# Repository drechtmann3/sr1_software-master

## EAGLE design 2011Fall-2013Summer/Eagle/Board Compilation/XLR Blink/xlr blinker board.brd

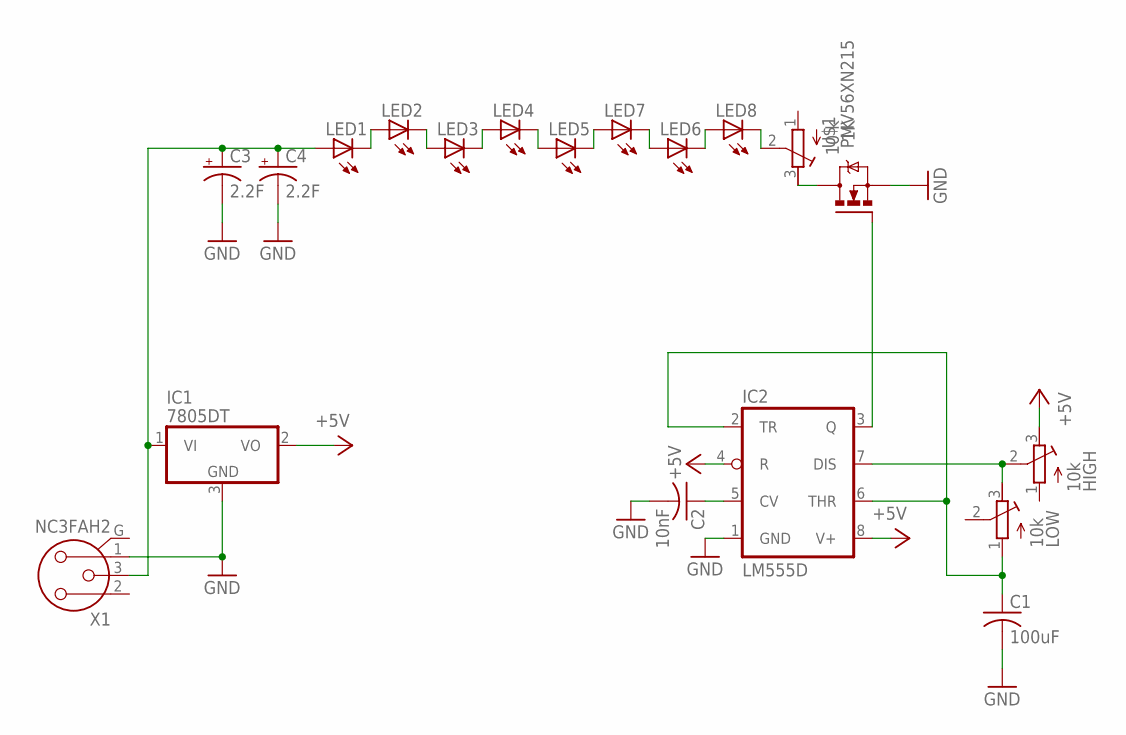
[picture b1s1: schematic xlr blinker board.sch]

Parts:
1K: 10 k; RTRIM3314J
C1: 100uF; C1206
C2: 10nF; C1206
C3, C4: 2.2F; E5-10,5
HIGH: 10k; RTRIM3314J
IC1: 7805DT; TO252
IC2: LM555D; SO08
LED1, LED2, LED3, LED4, LED5, LED6, LED7, LED8: LEDCHIPLED_1206; CHIPLED_1206
LOW: 10k; RTRIM3314J
U$1: PMV56XN215; SOT23; PART_NUM PMV56XN,215
X1: NC3FAH2

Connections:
24V: C3.+, C4.+, IC1.1 (VI), LED1.A, X1.3
+5V: HIGH.3 (A), IC1.2 (VO), IC2.4 (R), IC2.8 (V+)
GND: C1.2, C2.2, C3.-, C4.-, IC1.3 (GND), IC2.1 (GND), U$1.2 (S), X1.1 (2)
unnamed: HIGH.2 (S), IC2.7 (DIS), LOW.3 (A)
unnamed: C1.1, IC2.2 (TR), IC2.6 (THR), LOW.1 (E)
unnamed: C2.1, IC2.5 (CV)
unnamed: 1K.2 (S), LED8.C
unnamed: LED1.C, LED2.A
unnamed: 1K.3 (A), U$1.3 (D)
unnamed: IC2.3 (Q), U$1.1 (G)
unnamed: LED2.C, LED3.A
unnamed: LED3.C, LED4.A
unnamed: LED4.C, LED5.A
unnamed: LED5.C, LED7.A
unnamed: LED6.A, LED7.C
unnamed: LED6.C, LED8.A

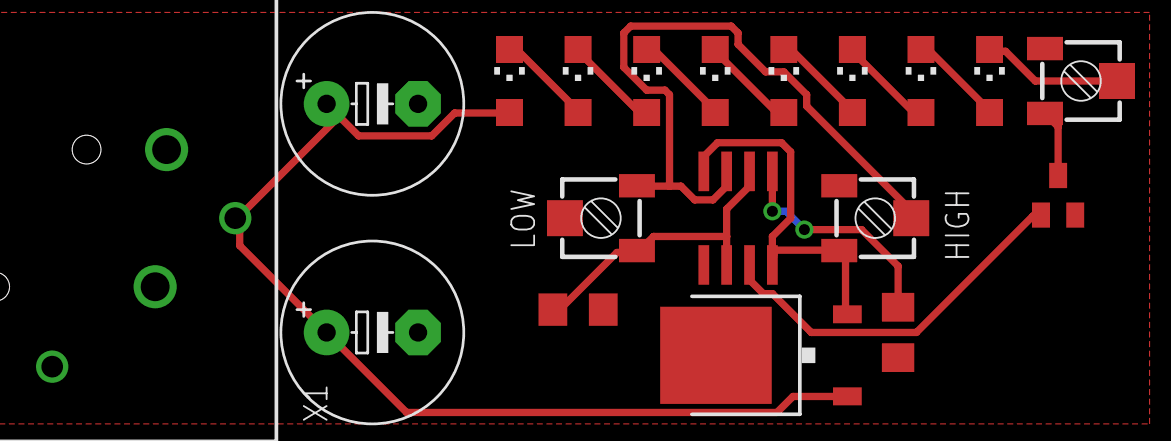
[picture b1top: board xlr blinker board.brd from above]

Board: 2 copper layers, 19 parts (0 on the bottom side), 16 nets.

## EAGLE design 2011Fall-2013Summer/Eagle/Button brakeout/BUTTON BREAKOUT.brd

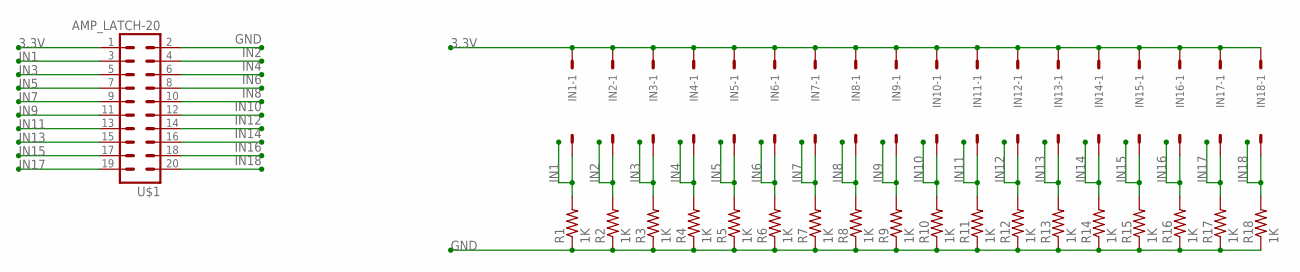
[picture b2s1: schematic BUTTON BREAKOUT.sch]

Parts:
IN1, IN2, IN3, IN4, IN5, IN6, IN7, IN8, IN9, IN10, IN11, IN12, IN13, IN14, IN15, IN16, IN17, IN18: C-GRID-02-70543; 70543-02
R1, R2, R3, R4, R5, R6, R7, R8, R9, R10, R11, R12, R13, R14, R15, R16, R17, R18: 1K; R1206
U$1: AMP_LATCH-20; MA10-2

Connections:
3.3V: IN1.1, IN2.1, IN3.1, IN4.1, IN5.1, IN6.1, IN7.1, IN8.1, IN9.1, IN10.1, IN11.1, IN12.1, IN13.1, IN14.1, IN15.1, IN16.1, IN17.1, IN18.1, U$1.1
GND: R1.1, R2.1, R3.1, R4.1, R5.1, R6.1, R7.1, R8.1, R9.1, R10.1, R11.1, R12.1, R13.1, R14.1, R15.1, R16.1, R17.1, R18.1, U$1.2
IN1: IN1.2, R1.2, U$1.3
IN2: IN2.2, R2.2, U$1.4
IN3: IN3.2, R3.2, U$1.5
IN4: IN4.2, R4.2, U$1.6
IN5: IN5.2, R5.2, U$1.7
IN6: IN6.2, R6.2, U$1.8
IN7: IN7.2, R7.2, U$1.9
IN8: IN8.2, R8.2, U$1.10
IN9: IN9.2, R9.2, U$1.11
IN10: IN10.2, R10.2, U$1.12
IN11: IN11.2, R11.2, U$1.13
IN12: IN12.2, R12.2, U$1.14
IN13: IN13.2, R13.2, U$1.15
IN14: IN14.2, R14.2, U$1.16
IN15: IN15.2, R15.2, U$1.17
IN16: IN16.2, R16.2, U$1.18
IN17: IN17.2, R17.2, U$1.19
IN18: IN18.2, R18.2, U$1.20

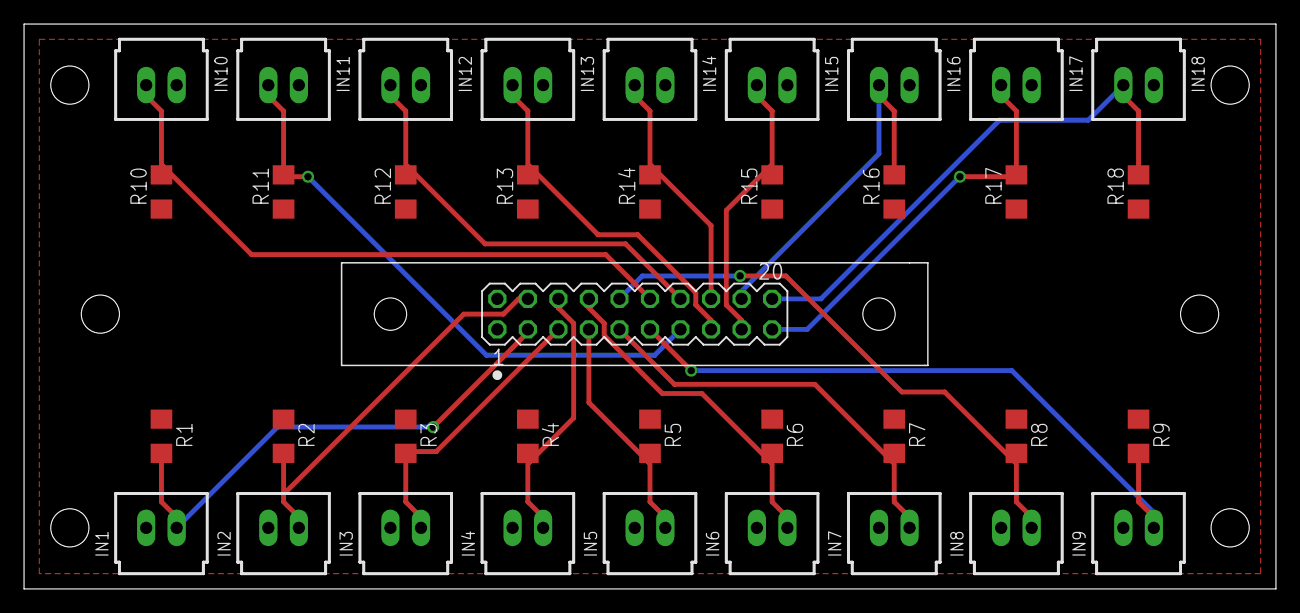
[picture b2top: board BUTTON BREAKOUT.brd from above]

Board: 2 copper layers, 104.1 x 47.0 mm, 37 parts (0 on the bottom side), 20 nets.

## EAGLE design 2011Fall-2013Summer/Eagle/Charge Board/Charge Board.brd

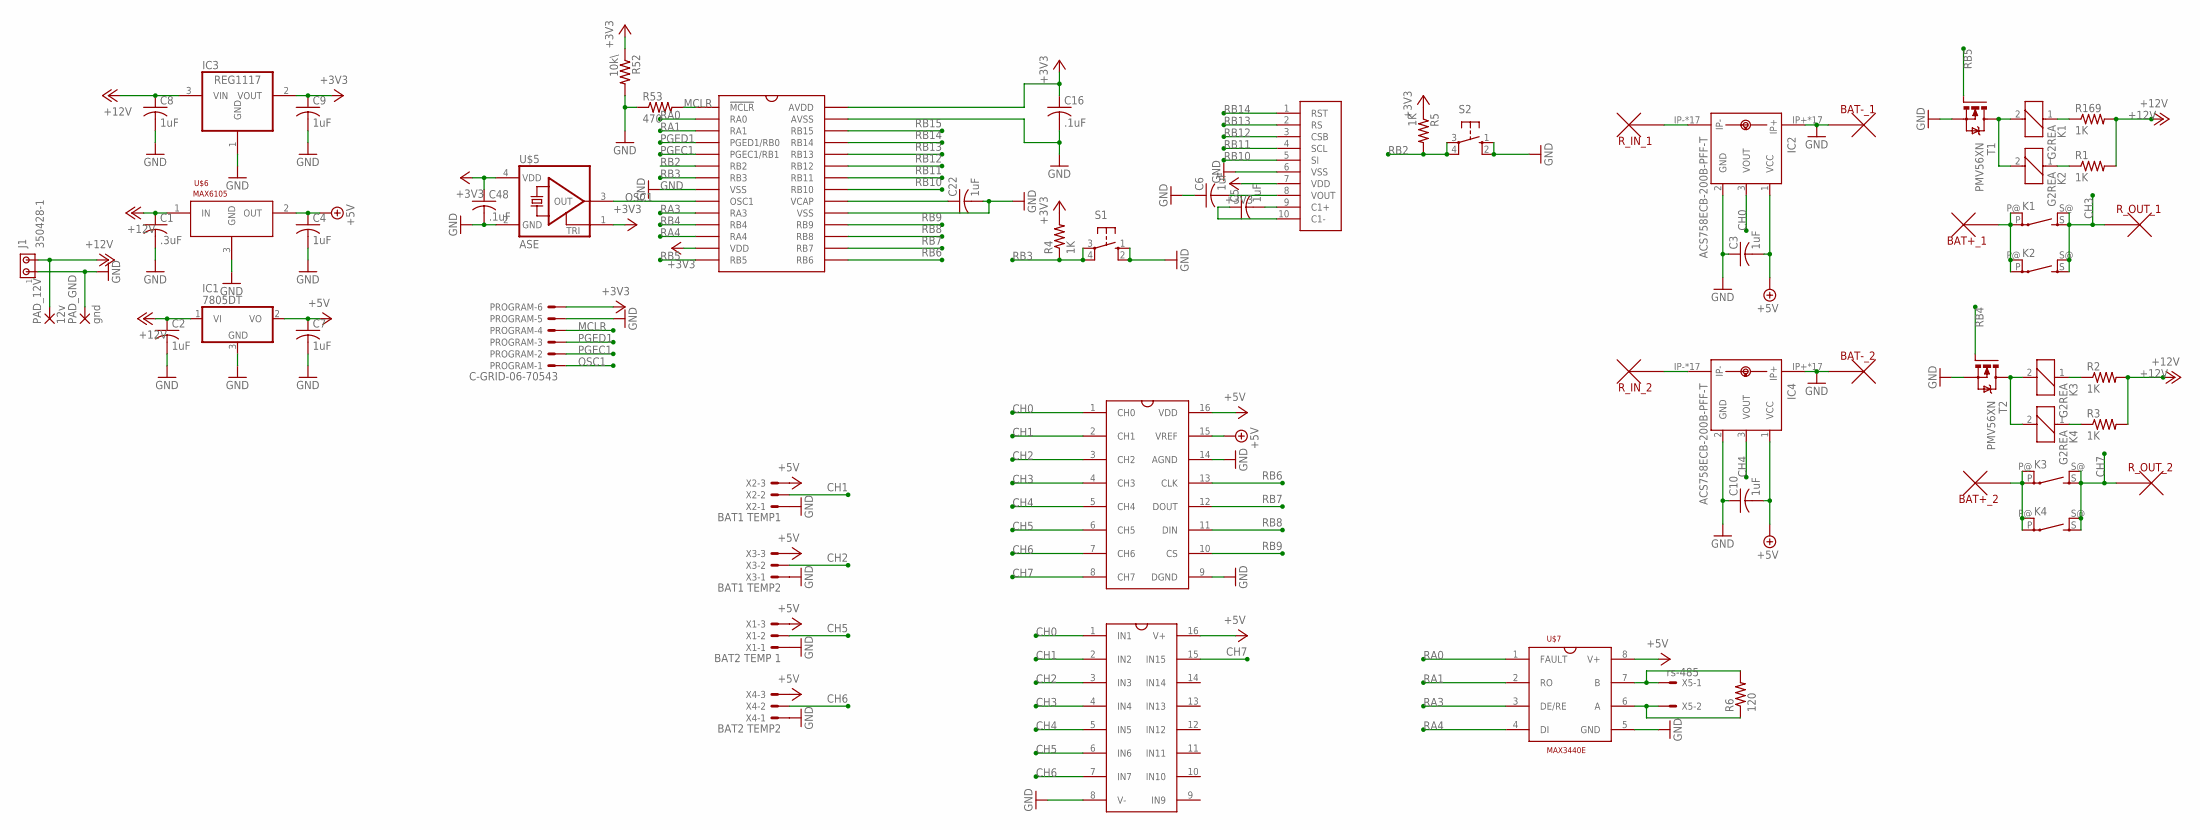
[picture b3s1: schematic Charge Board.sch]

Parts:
BAT+_1: BAT1 +; SOLDERPAD
BAT+_2: BAT2 +; SOLDERPAD
BAT-_1: BAT1 GND; SOLDERPAD
BAT-_2: BAT2 GND; SOLDERPAD
C1: .3uF; C1206
C2, C3, C4, C5, C6, C7, C8, C9, C10, C22: 1uF; C1206
C16, C48: .1uF; C1206
IC1: 7805DT; TO252
IC2, IC4: ACS758ECB-200B-PFF-T; CB-PFF
IC3: REG1117; SOT223
J1: 350428-1
K1, K2, K3, K4: G2REA
PAD_12V: 12v; 3,81/1,4
PAD_GND: gnd; 3,81/1,4
PROGRAM: C-GRID-06-70543; 70543-06
R1, R2, R3, R4, R5, R169: 1K; R1206
R6: 120; R1206
R52: 10k\; R1206
R53: 470; R1206
R_IN_1: R1 IN; SOLDERPAD
R_IN_2: R2 IN; SOLDERPAD
R_OUT_1: R1 OUT; SOLDERPAD
R_OUT_2: R2 OUT; SOLDERPAD
S1, S2: 10-XX; B3F-10XX
T1, T2: PMV56XN; SOT23
U$1: MCP-3008; SO16
U$2: LCD_SCREEN
U$3: SP720APP; SO16
U$4: PIC24HJ128GP-202; SO28W
U$5: ASE
U$6: MAX6105; SOT23
U$7: MAX3440E; SO-08
X1: BAT2 TEMP 1; 70543-03
X2: BAT1 TEMP1; 70543-03
X3: BAT1 TEMP2; 70543-03
X4: BAT2 TEMP2; 70543-03
X5: rs-485; 70543-02

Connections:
+3V3: C9.1, C16.1, C48.1, IC3.2 (VOUT), PROGRAM.6, R4.2, R5.1, R52.1, U$2.7 (VDD), U$4.13 (VDD), U$4.28 (AVDD), U$5.1 (TRI), U$5.4 (VDD)
+5V: C3.2, C4.1, C7.1, C10.2, IC1.2 (VO), IC2.1 (VCC), IC4.1 (VCC), U$1.15 (VREF), U$1.16 (VDD), U$3.16 (V+), U$6.2 (OUT), U$7.8 (V+), X1.3, X2.3, X3.3, X4.3
+12V: C1.1, C2.1, C8.1, IC1.1 (VI), IC3.3 (VIN), J1.2, PAD_12V.1, R1.2, R2.2, R3.2, R169.2, U$6.1 (IN)
CH0: IC2.3 (VOUT), U$1.1 (CH0), U$3.1 (IN1)
CH1: U$1.2 (CH1), U$3.2 (IN2), X2.2
CH2: U$1.3 (CH2), U$3.3 (IN3), X3.2
CH3: K1.S, K1.S@ (S), K2.S, K2.S@ (S), R_OUT_1.P$1, U$1.4 (CH3), U$3.4 (IN4)
CH4: IC4.3 (VOUT), U$1.5 (CH4), U$3.5 (IN5)
CH5: U$1.6 (CH5), U$3.6 (IN6), X1.2
CH6: U$1.7 (CH6), U$3.7 (IN7), X4.2
CH7: K3.S, K3.S@ (S), K4.S, K4.S@ (S), R_OUT_2.P$1, U$1.8 (CH7), U$3.15 (IN15)
GND: BAT-_1.P$1, BAT-_2.P$1, C1.2, C2.2, C3.1, C4.2, C6.1, C7.2, C8.2, C9.2, C10.1, C16.2, C22.2, C48.2, IC1.3 (GND), IC2.2 (GND), IC2.IP+, IC2.IP+@2 (IP+), IC2.IP+@3 (IP+), IC2.IP+@4 (IP+), IC2.IP+@5 (IP+), IC2.IP+@6 (IP+), IC2.IP+@7 (IP+), IC2.IP+@8 (IP+), IC2.IP+@9 (IP+), IC2.IP+@10 (IP+), IC2.IP+@11 (IP+), IC2.IP+@12 (IP+), IC2.IP+@13 (IP+), IC2.IP+@14 (IP+), IC2.IP+@15 (IP+), IC2.IP+@16 (IP+), IC2.IP+@17 (IP+), IC3.1 (GND), IC4.2 (GND), IC4.IP+, IC4.IP+@2 (IP+), IC4.IP+@3 (IP+), IC4.IP+@4 (IP+), IC4.IP+@5 (IP+), IC4.IP+@6 (IP+), IC4.IP+@7 (IP+), IC4.IP+@8 (IP+), IC4.IP+@9 (IP+), IC4.IP+@10 (IP+), IC4.IP+@11 (IP+), IC4.IP+@12 (IP+), IC4.IP+@13 (IP+), IC4.IP+@14 (IP+), IC4.IP+@15 (IP+), IC4.IP+@16 (IP+), IC4.IP+@17 (IP+), J1.1, PAD_GND.1, PROGRAM.5, R52.2, R53.1, S1.1 (S), S1.2 (S1), S2.1 (S), S2.2 (S1), T1.2 (S), T2.2 (S), U$1.9 (DGND), U$1.14 (AGND), U$2.6 (VSS), U$3.8 (V-), U$4.8 (VSS), U$4.19 (VSS), U$4.27 (AVSS), U$5.2 (GND), U$6.3 (GND), U$7.5 (GND), X1.1, X2.1, X3.1, X4.1
MCLR: PROGRAM.4, R53.2, U$4.1 (!MCLR!)
unnamed: K1.2, K2.2, T1.3 (D)
unnamed: K2.1, R1.1
unnamed: BAT+_2.P$1, K3.P, K3.P@, K4.P, K4.P@
unnamed: K3.1, R2.1
unnamed: K3.2, K4.2, T2.3 (D)
unnamed: K4.1, R3.1
unnamed: IC4.IP-, IC4.IP-@2 (IP-), IC4.IP-@3 (IP-), IC4.IP-@4 (IP-), IC4.IP-@5 (IP-), IC4.IP-@6 (IP-), IC4.IP-@7 (IP-), IC4.IP-@8 (IP-), IC4.IP-@9 (IP-), IC4.IP-@10 (IP-), IC4.IP-@11 (IP-), IC4.IP-@12 (IP-), IC4.IP-@13 (IP-), IC4.IP-@14 (IP-), IC4.IP-@15 (IP-), IC4.IP-@16 (IP-), IC4.IP-@17 (IP-), R_IN_2.P$1
unnamed: IC2.IP-, IC2.IP-@2 (IP-), IC2.IP-@3 (IP-), IC2.IP-@4 (IP-), IC2.IP-@5 (IP-), IC2.IP-@6 (IP-), IC2.IP-@7 (IP-), IC2.IP-@8 (IP-), IC2.IP-@9 (IP-), IC2.IP-@10 (IP-), IC2.IP-@11 (IP-), IC2.IP-@12 (IP-), IC2.IP-@13 (IP-), IC2.IP-@14 (IP-), IC2.IP-@15 (IP-), IC2.IP-@16 (IP-), IC2.IP-@17 (IP-), R_IN_1.P$1
unnamed: C6.2, U$2.8 (VOUT)
unnamed: C5.2, U$2.9 (C1+)
unnamed: C5.1, U$2.10 (C1-)
unnamed: C22.1, U$4.20 (VCAP)
unnamed: K1.1, R169.1
unnamed: R6.2, U$7.7 (B), X5.1
unnamed: R6.1, U$7.6 (A), X5.2
unnamed: BAT+_1.P$1, K1.P, K1.P@, K2.P, K2.P@
OSC1: PROGRAM.1, U$4.9 (OSC1), U$5.3 (OUT)
PGEC1: PROGRAM.2, U$4.5 (PGEC1/RB1)
PGED1: PROGRAM.3, U$4.4 (PGED1/RB0)
RA0: U$4.2 (RA0), U$7.1 (FAULT)
RA1: U$4.3 (RA1), U$7.2 (RO)
RA3: U$4.10 (RA3), U$7.3 (DE/RE)
RA4: U$4.12 (RA4), U$7.4 (DI)
RB2: R5.2, S2.3, S2.4 (P1), U$4.6 (RB2)
RB3: R4.1, S1.3, S1.4 (P1), U$4.7 (RB3)
RB4: T2.1 (G), U$4.11 (RB4)
RB5: T1.1 (G), U$4.14 (RB5)
RB6: U$1.13 (CLK), U$4.15 (RB6)
RB7: U$1.12 (DOUT), U$4.16 (RB7)
RB8: U$1.11 (DIN), U$4.17 (RB8)
RB9: U$1.10 (CS), U$4.18 (RB9)
RB10: U$2.5 (SI), U$4.21 (RB10)
RB11: U$2.4 (SCL), U$4.22 (RB11)
RB12: U$2.3 (CSB), U$4.23 (RB12)
RB13: U$2.2 (RS), U$4.24 (RB13)
RB14: U$2.1 (RST), U$4.25 (RB14)
RB15: U$4.26 (RB15)

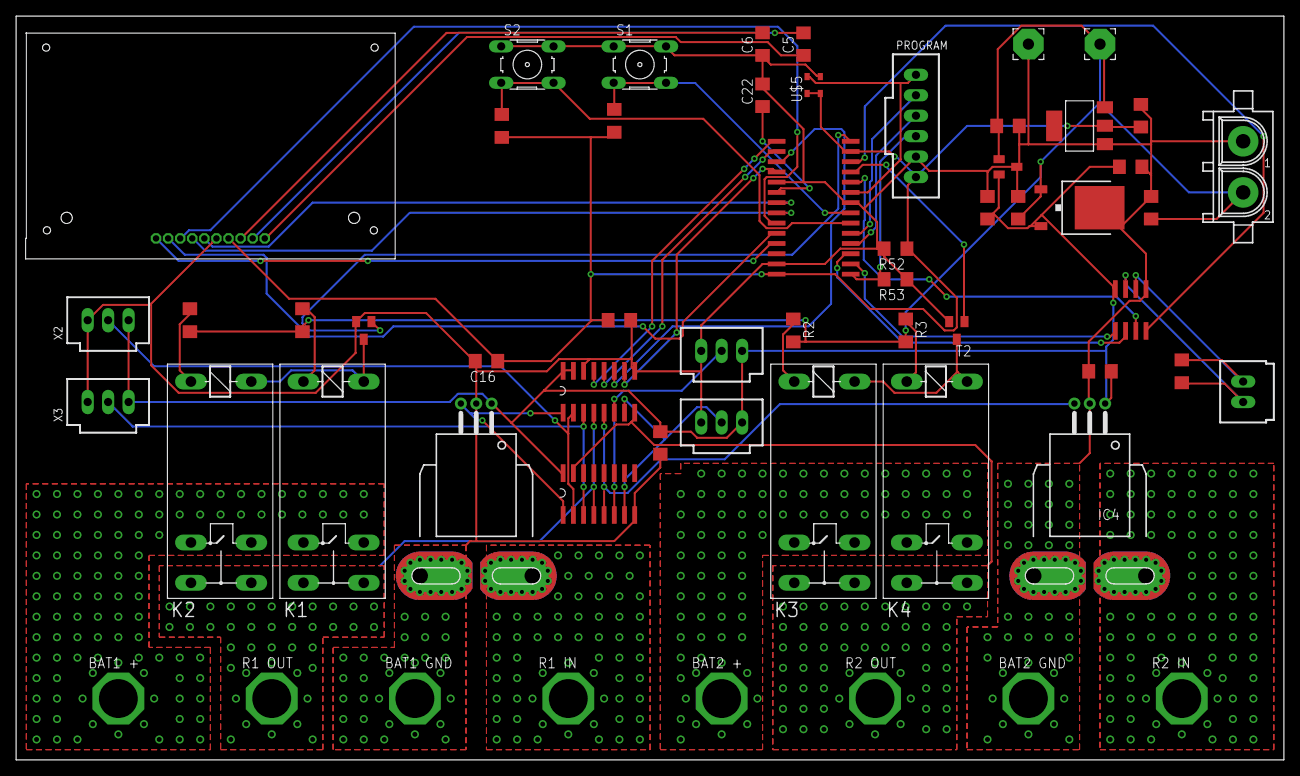
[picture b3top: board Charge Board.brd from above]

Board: 2 copper layers, 157.5 x 92.4 mm, 58 parts (0 on the bottom side), 49 nets.

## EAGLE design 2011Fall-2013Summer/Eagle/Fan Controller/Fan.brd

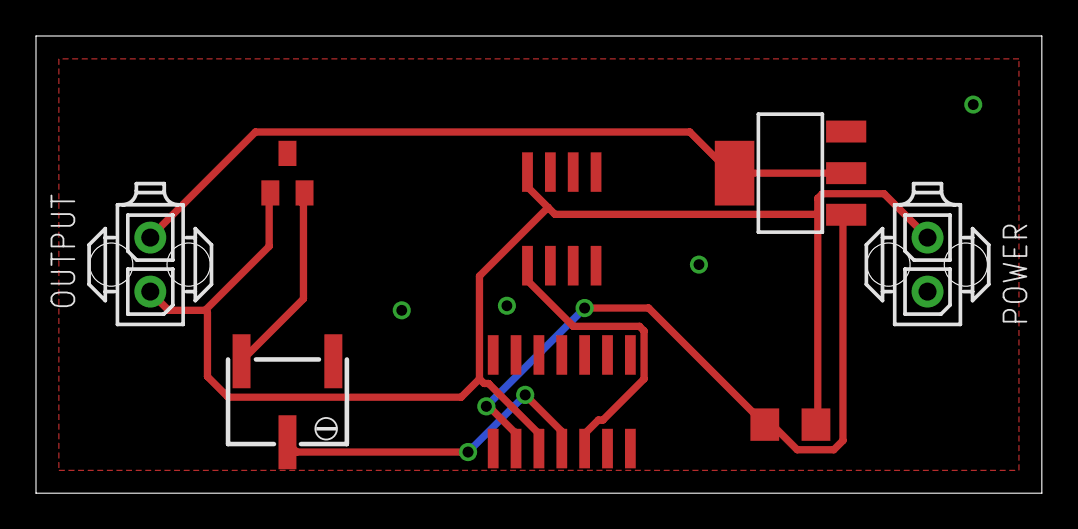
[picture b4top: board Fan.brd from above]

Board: 2 copper layers, 55.9 x 25.4 mm, 8 parts (0 on the bottom side), 7 nets.

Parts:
IC1: LM339D; SO14
OUTPUT: 794681-2
POWER: 794681-2
R1: 10k; RTRIMTS63Y
U$1: 100; R1206
U$2: MAX6103; SOT23
U$3: NDT3055; SOT223
U$4: LM35; SO-08

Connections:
12V: IC1.3, OUTPUT.1, POWER.2, U$1.2, U$2.1, U$4.8
GND: IC1.12, POWER.1, R1.1, U$2.3, U$3.3, U$4.4
unnamed: IC1.2, U$1.1, U$3.1
unnamed: IC1.4, R1.2
unnamed: R1.3, U$2.2
unnamed: OUTPUT.2, U$3.2, U$3.4
unnamed: IC1.5, U$4.1

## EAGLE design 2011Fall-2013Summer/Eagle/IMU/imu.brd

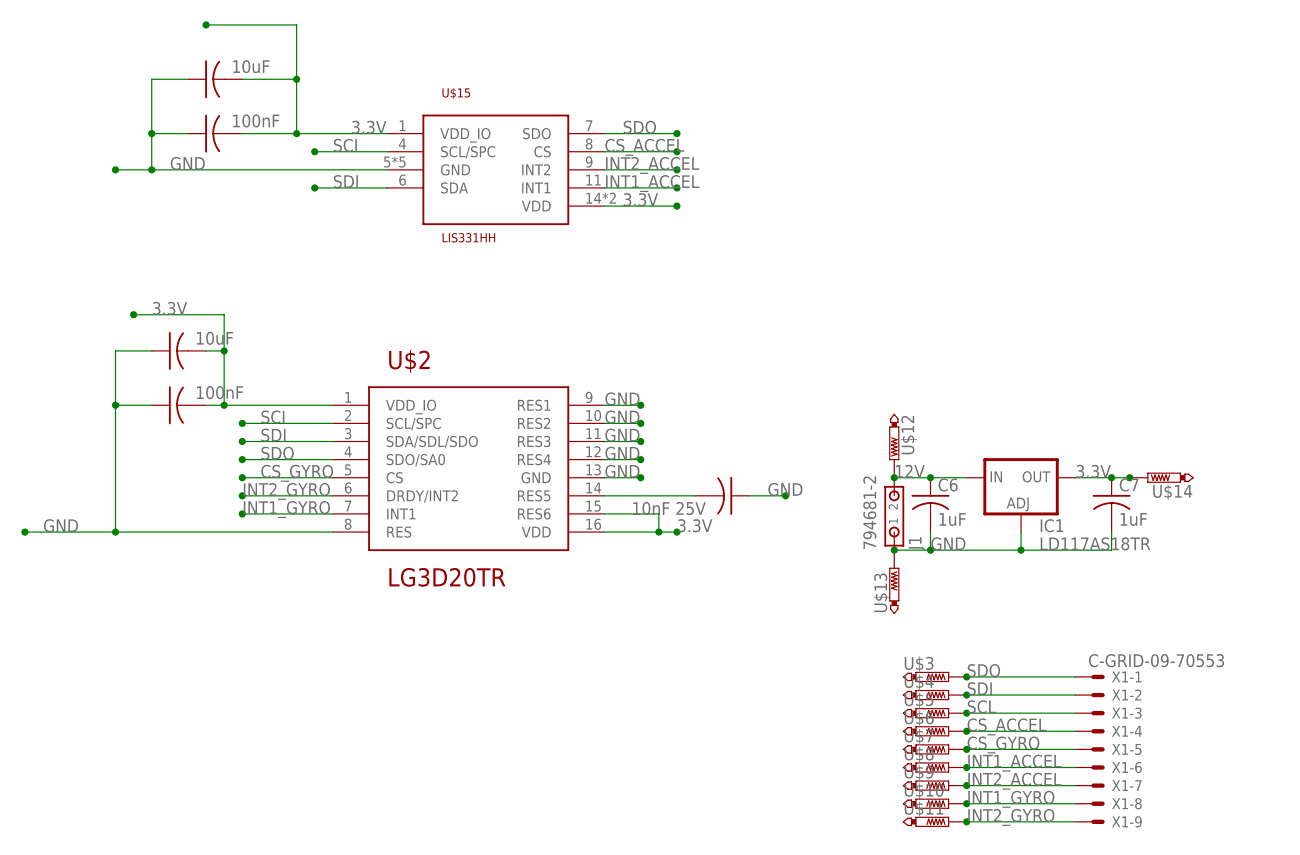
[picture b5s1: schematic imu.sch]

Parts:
C1_1: 10nF 25V; C1206
C2_1, C4_1: 10uF; C1206
C3_1, C5_1: 100nF; C1206
C6, C7: 1uF; C1206
IC1: LD117AS18TR; SOT223
J1: 794681-2
U$2: LG3D20TR; L3GD20TR
U$3, U$4, U$5, U$6, U$7, U$8, U$9, U$10, U$11, U$12, U$13, U$14: TESTPAD-20MIL; 20MIL
U$15: LIS331HH
X1: C-GRID-09-70553; 70553-09

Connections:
3.3V: C2_1.2, C3_1.2, C4_1.2, C5_1.2, C7.1, IC1.4 (OUT), U$2.1 (VDD_IO), U$2.15 (RES6), U$2.16 (VDD), U$14.P$1, U$15.1 (VDD_IO), U$15.14 (VDD), U$15.15 (VDD)
12V: C6.1, IC1.3 (IN), J1.2, U$12.P$1
CS_ACCEL: U$6.P$1, U$15.8 (CS), X1.4
CS_GYRO: U$2.5 (CS), U$7.P$1, X1.5
GND: C1_1.1, C2_1.1, C3_1.1, C4_1.1, C5_1.1, C6.2, C7.2, IC1.1 (ADJ), J1.1, U$2.8 (RES), U$2.9 (RES1), U$2.10 (RES2), U$2.11 (RES3), U$2.12 (RES4), U$2.13 (GND), U$13.P$1, U$15.5 (GND), U$15.10 (GND), U$15.12 (GND), U$15.13 (GND), U$15.16 (GND)
INT1_ACCEL: U$8.P$1, U$15.11 (INT1), X1.6
INT1_GYRO: U$2.7 (INT1), U$10.P$1, X1.8
INT2_ACCEL: U$9.P$1, U$15.9 (INT2), X1.7
INT2_GYRO: U$2.6 (DRDY/INT2), U$11.P$1, X1.9
SCI: U$2.2 (SCL/SPC), U$15.4 (SCL/SPC)
SCL: U$5.P$1, X1.3
SDI: U$2.3 (SDA/SDL/SDO), U$4.P$1, U$15.6 (SDA), X1.2
SDO: U$2.4 (SDO/SA0), U$3.P$1, U$15.7 (SDO), X1.1
VOUT: C1_1.2, U$2.14 (RES5)

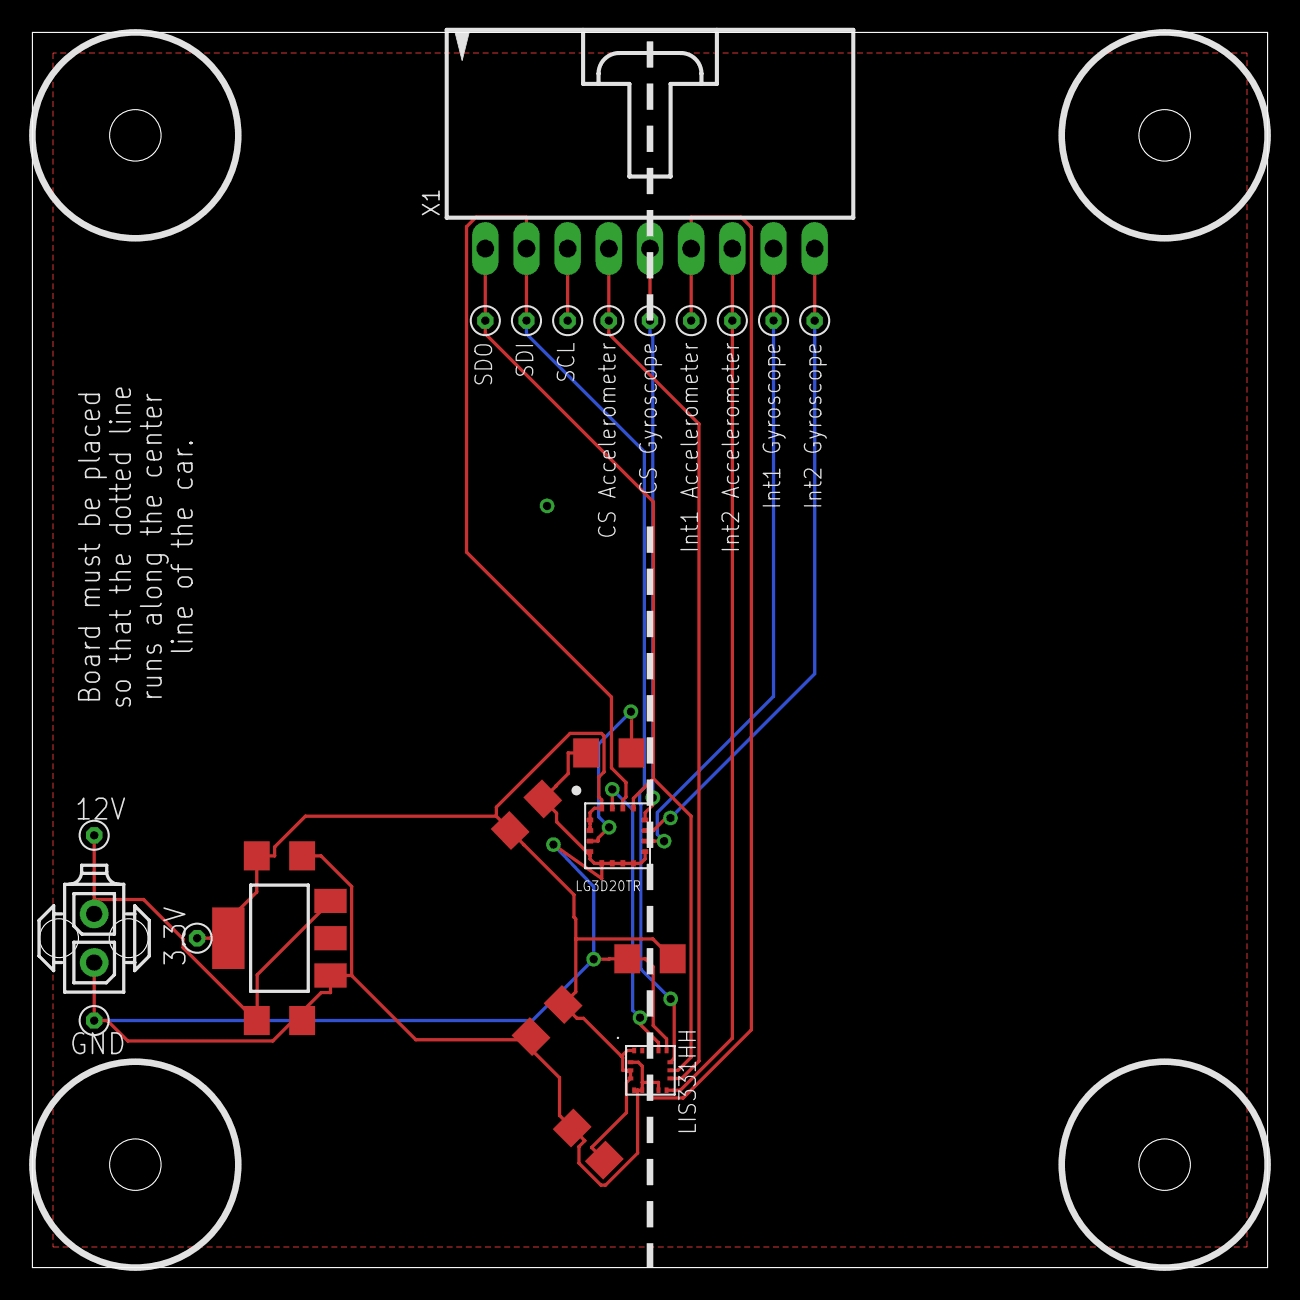
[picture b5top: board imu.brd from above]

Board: 2 copper layers, 76.2 x 76.2 mm, 24 parts (0 on the bottom side), 14 nets.

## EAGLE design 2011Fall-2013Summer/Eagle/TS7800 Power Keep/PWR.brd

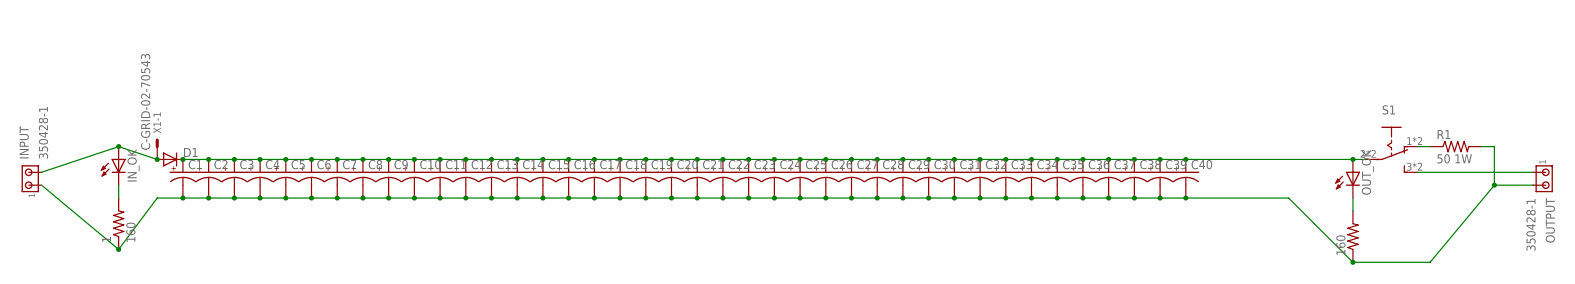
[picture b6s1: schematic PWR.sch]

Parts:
1: 160; R1206
160: R-US_R1206; R1206
C1, C2, C3, C4, C5, C6, C7, C8, C9, C10, C11, C12, C13, C14, C15, C16, C17, C18, C19, C20, C21, C22, C23, C24, C25, C26, C27, C28, C29, C30, C31, C32, C33, C34, C35, C36, C37, C38, C39, C40: CPOL-USE5-10.5; E5-10,5
D1: DIODE-SOD123; SOD123
INPUT: 350428-1
IN_OK: LEDCHIPLED_1206; CHIPLED_1206
OUTPUT: 350428-1
OUT_OK: LEDCHIPLED_1206; CHIPLED_1206
R1: 50 1W; WSC2515
S1: M251; SLIDE_SWITCH
X1: C-GRID-02-70543; 70543-02

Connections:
5V: C1.+, C2.+, C3.+, C4.+, C5.+, C6.+, C7.+, C8.+, C9.+, C10.+, C11.+, C12.+, C13.+, C14.+, C15.+, C16.+, C17.+, C18.+, C19.+, C20.+, C21.+, C22.+, C23.+, C24.+, C25.+, C26.+, C27.+, C28.+, C29.+, C30.+, C31.+, C32.+, C33.+, C34.+, C35.+, C36.+, C37.+, C38.+, C39.+, C40.+, D1.C, OUT_OK.A, S1.2, S1.5
GND: 1.1, 160.1, C1.-, C2.-, C3.-, C4.-, C5.-, C6.-, C7.-, C8.-, C9.-, C10.-, C11.-, C12.-, C13.-, C14.-, C15.-, C16.-, C17.-, C18.-, C19.-, C20.-, C21.-, C22.-, C23.-, C24.-, C25.-, C26.-, C27.-, C28.-, C29.-, C30.-, C31.-, C32.-, C33.-, C34.-, C35.-, C36.-, C37.-, C38.-, C39.-, C40.-, INPUT.1, OUTPUT.2, R1.2
unnamed: R1.1, S1.1 (O), S1.6 (O)
unnamed: 1.2, IN_OK.C
unnamed: 160.2, OUT_OK.C
unnamed: OUTPUT.1, S1.3 (S), S1.4 (S)
unnamed: D1.A, INPUT.2, IN_OK.A, X1.1

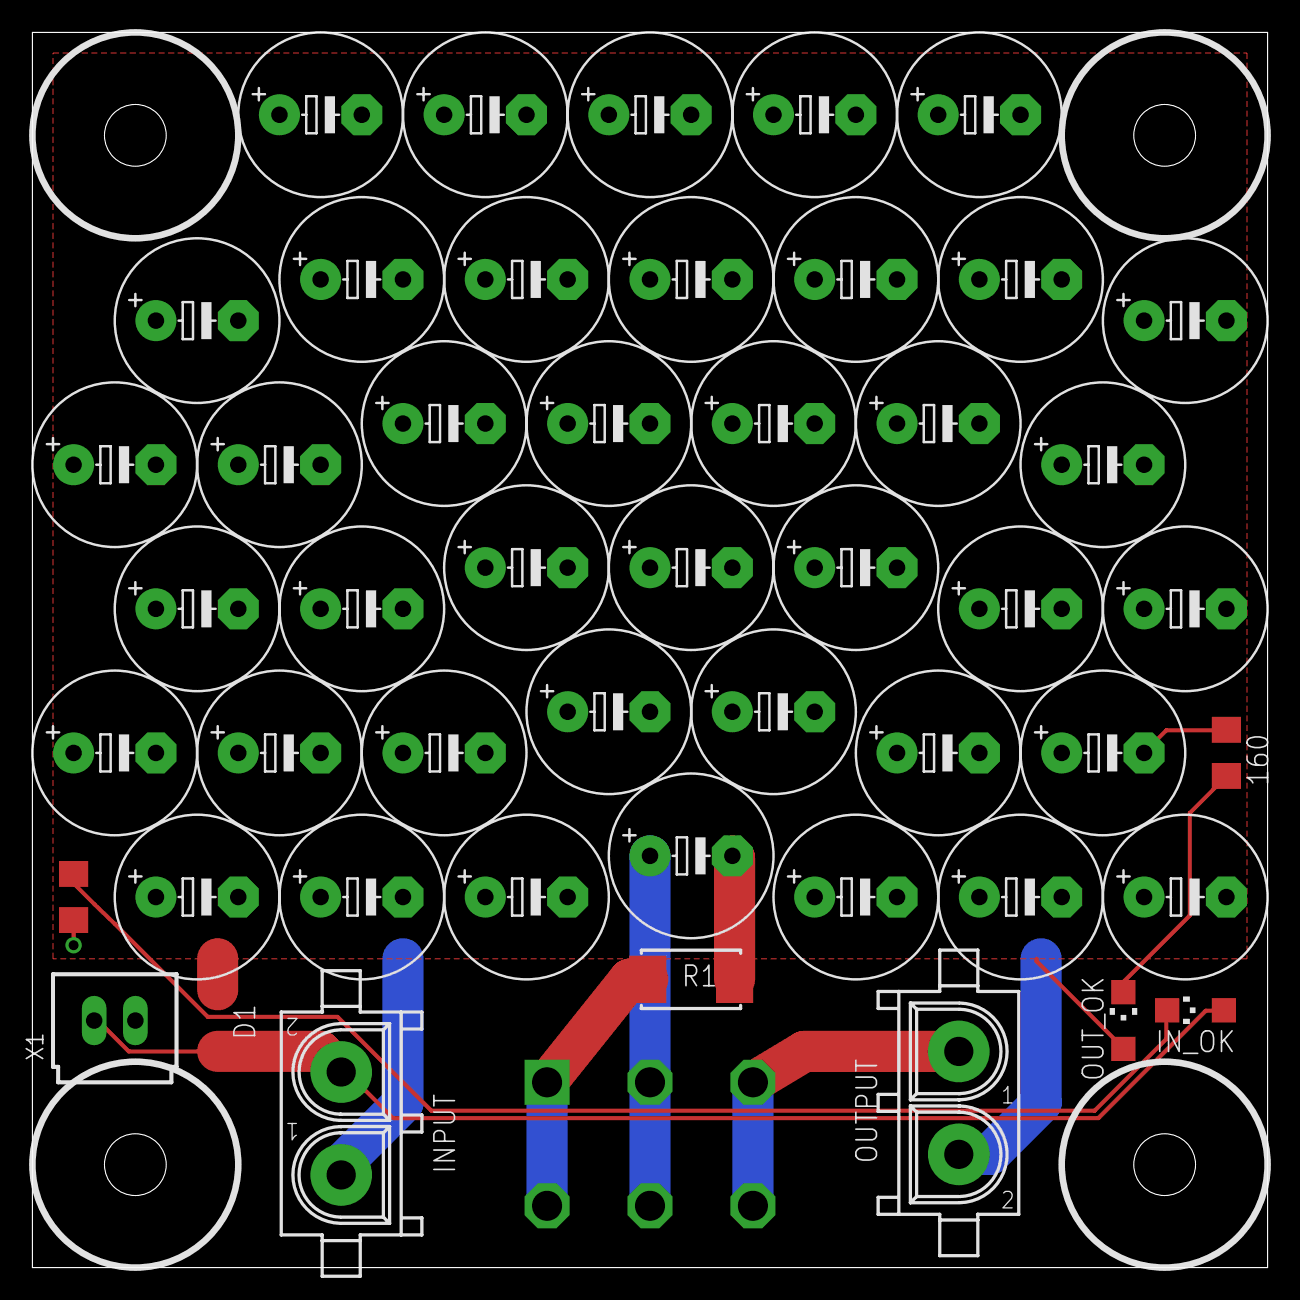
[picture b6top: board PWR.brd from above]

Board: 2 copper layers, 76.2 x 76.2 mm, 50 parts (1 on the bottom side), 7 nets.
